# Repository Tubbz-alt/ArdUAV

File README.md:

<br />

Code repository for ground station and flight control software for experimental Arduino UAVs (fixed wing).

# [Flight Test!](https://youtu.be/rPLp50zgQIw)

See https://forum.flitetest.com/index.php?threads/arduino-scratch-build-screamin-seagull-ii.57977/ for the most recent ArdUAV plane build log.

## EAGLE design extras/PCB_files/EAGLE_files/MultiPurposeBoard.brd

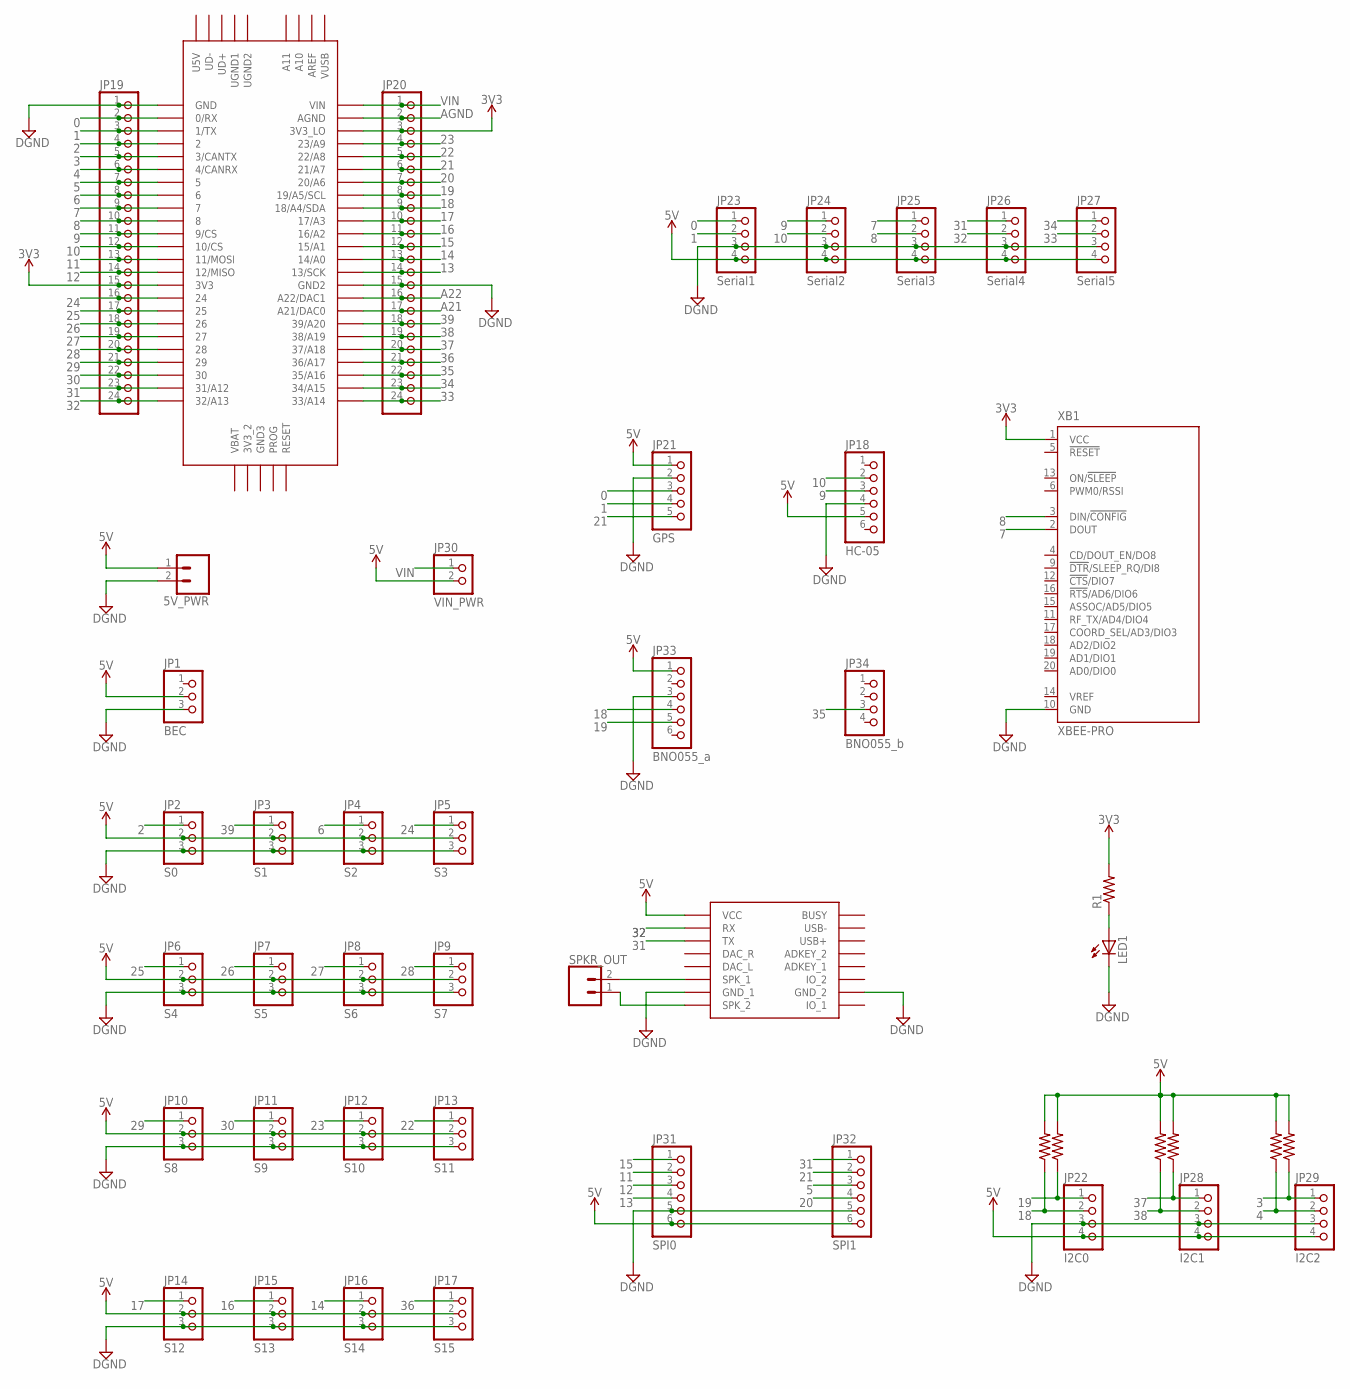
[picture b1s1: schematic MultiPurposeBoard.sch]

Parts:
5V_PWR: CONN_025MM; SCREWTERMINAL-5MM-2
JP1: BEC; 1X03
JP2: S0; 1X03
JP3: S1; 1X03
JP4: S2; 1X03
JP5: S3; 1X03
JP6: S4; 1X03
JP7: S5; 1X03
JP8: S6; 1X03
JP9: S7; 1X03
JP10: S8; 1X03
JP11: S9; 1X03
JP12: S10; 1X03
JP13: S11; 1X03
JP14: S12; 1X03
JP15: S13; 1X03
JP16: S14; 1X03
JP17: S15; 1X03
JP18: HC-05; 1X06
JP19, JP20: PINHD-1X24; 1X24
JP21: GPS; 1X05
JP22: I2C0; 1X04
JP23: Serial1; 1X04
JP24: Serial2; 1X04
JP25: Serial3; 1X04
JP26: Serial4; 1X04
JP27: Serial5; 1X04
JP28: I2C1; 1X04
JP29: I2C2; 1X04
JP30: VIN_PWR; 1X02
JP31: SPI0; 1X06
JP32: SPI1; 1X06
JP33: BNO055_a; 1X06
JP34: BNO055_b; 1X04
LED1: LED5MM
R1, R2, R3, R4, R5, R6, R7: R-US_0207/12; 0207/12
SPKR_OUT: CONN_025MM; SCREWTERMINAL-5MM-2
U$1: TEENSY_3.5/3.6
U$2: DFPLAYER
XB1: XBEE-PRO

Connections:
0: JP19.2, JP21.3, JP23.1, U$1.0/RX
1: JP19.3, JP21.4, JP23.2, U$1.1/TX
2: JP2.1, JP19.4, U$1.2
3: JP19.5, JP29.1, R5.1, U$1.3/CANTX
4: JP19.6, JP29.2, R7.1, U$1.4/CANRX
5: JP19.7, JP32.3, U$1.5
5V: 5V_PWR.1, JP1.2, JP2.2, JP3.2, JP4.2, JP5.2, JP6.2, JP7.2, JP8.2, JP9.2, JP10.2, JP11.2, JP12.2, JP13.2, JP14.2, JP15.2, JP16.2, JP17.2, JP18.5, JP21.1, JP22.4, JP23.4, JP24.4, JP25.4, JP26.4, JP27.4, JP28.4, JP29.4, JP30.2, JP31.6, JP32.6, JP33.1, R2.2, R3.2, R4.2, R5.2, R6.2, R7.2, U$2.VCC
6: JP4.1, JP19.8, U$1.6
7: JP19.9, JP25.1, U$1.7, XB1.2 (DOUT)
8: JP19.10, JP25.2, U$1.8, XB1.3 (DIN/!CONFIG)
9: JP18.3, JP19.11, JP24.1, U$1.9/CS
10: JP18.2, JP19.12, JP24.2, U$1.10/CS
11: JP19.13, JP31.2, U$1.11/MOSI
12: JP19.14, JP31.3, U$1.12/MISO
13: JP20.14, JP31.4, U$1.13/SCK
14: JP16.1, JP20.13, U$1.14/A0
15: JP20.12, JP31.1, U$1.15/A1
16: JP15.1, JP20.11, U$1.16/A2
17: JP14.1, JP20.10, U$1.17/A3
18: JP20.9, JP22.2, JP33.4, R2.1, U$1.18/A4/SDA
19: JP20.8, JP22.1, JP33.5, R3.1, U$1.19/A5/SCL
20: JP20.7, JP32.4, U$1.20/A6
21: JP20.6, JP21.5, JP32.2, U$1.21/A7
22: JP13.1, JP20.5, U$1.22/A8
23: JP12.1, JP20.4, U$1.23/A9
24: JP5.1, JP19.16, U$1.24
25: JP6.1, JP19.17, U$1.25
26: JP7.1, JP19.18, U$1.26
27: JP8.1, JP19.19, U$1.27
28: JP9.1, JP19.20, U$1.28
29: JP10.1, JP19.21, U$1.29
30: JP11.1, JP19.22, U$1.30
31: JP19.23, JP26.1, JP32.1, U$1.31/A12, U$2.TX
32: JP19.24, JP26.2, U$1.32/A13, U$2.RX
33: JP20.24, JP27.2, U$1.33/A14
34: JP20.23, JP27.1, U$1.34/A15
35: JP20.22, JP34.3, U$1.35/A16
36: JP17.1, JP20.21, U$1.36/A17
37: JP20.20, JP28.1, R6.1, U$1.37/A18
38: JP20.19, JP28.2, R4.1, U$1.38/A19
39: JP3.1, JP20.18, U$1.39/A20
A21: JP20.17, U$1.21/DAC0 (A21/DAC0)
A22: JP20.16, U$1.A22/DAC1
AGND: JP20.2, U$1.AGND
DGND: 5V_PWR.2, JP1.3, JP2.3, JP3.3, JP4.3, JP5.3, JP6.3, JP7.3, JP8.3, JP9.3, JP10.3, JP11.3, JP12.3, JP13.3, JP14.3, JP15.3, JP16.3, JP17.3, JP18.4, JP19.1, JP20.15, JP21.2, JP22.3, JP23.3, JP24.3, JP25.3, JP26.3, JP27.3, JP28.3, JP29.3, JP31.5, JP32.5, JP33.3, LED1.K (C), U$1.GND, U$1.GND2, U$2.GND_1, U$2.GND_2, XB1.10 (GND)
unnamed: LED1.A, R1.1
unnamed: SPKR_OUT.2, U$2.SPK1 (SPK_1)
unnamed: SPKR_OUT.1, U$2.SPK2 (SPK_2)
VCC_2: JP19.15, JP20.3, R1.2, U$1.3V3, U$1.3V3_LO, XB1.1 (VCC)
VIN: JP20.1, JP30.1, U$1.VIN

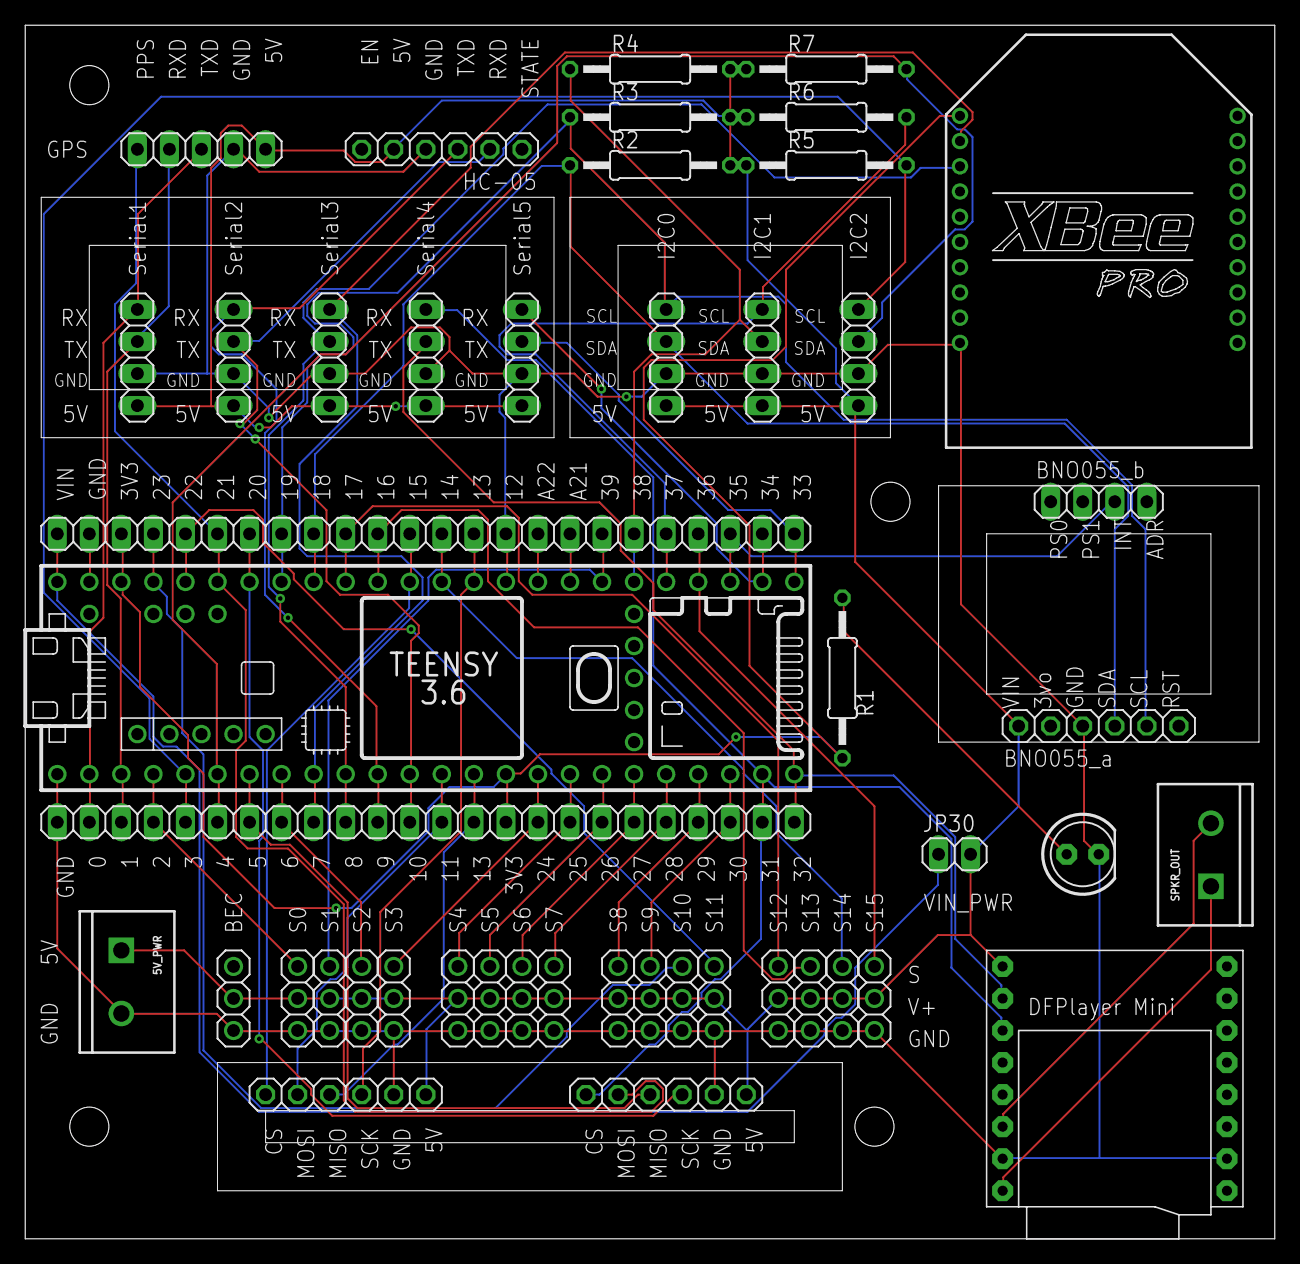
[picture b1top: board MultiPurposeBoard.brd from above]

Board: 2 copper layers, 99.0 x 96.2 mm, 47 parts (0 on the bottom side), 50 nets.

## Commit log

2019-04-17 Rename ArdUAV_Config/git_ArdUAV.bat to git_ArdUAV.bat
2019-04-20 Update and rename ArdUAV_Adafruit_PWMServoDriver.cpp to d
2019-06-22 Simplified serialEvent() contents
2019-06-22 Simplify serialEvent() contents
2019-06-22 Formatting
2019-06-22 Format
2019-06-22 Deconflict function names
2019-06-22 Deconflict function name
2019-06-22 bug fix
2019-07-06 spacing stuff/#pragma once
2019-07-31 Check Serial port compatibility at compile time
2019-07-31 Check compatible bauds for concurrent Serial port connections
2019-07-31 IDE Library Manager Compatibility Changes
2019-08-30 Added COBS encoding/decoding
2019-08-30 Parse UTC pieces
2019-08-30 Update telemetry struct
2019-08-30 Full GPS telemetry functionality added
2019-09-02 Rename extras/PCB_files/empty.txt to extras/PCB_files/Screamin_Eagle_II_files/empty.txt
2019-09-07 Added limits for extra servos
2019-09-07 Telemetry bug fixes
2019-09-08 Address Issue #9 - Increase IMU reading accuracy
    Calculate Euler angles from quaternions MCU-side instead of sensor-side
2019-09-08 Added Logo
2019-10-04 Added support for more NMEA sentences
2019-10-06 Deleted extra whitespace
2019-10-11 Default settings changes
2019-10-27 Added config file functionality
2019-10-27 Changed quotes to JSON format
2019-10-27 Added ability to save config file with custom name
2019-10-27 Added icon
2019-10-28 Bug fixes
2019-12-11 Bug fixes/changes in default settings
2019-12-11 Got rid of extra imports
2019-12-11 Changed defaults
2019-12-11 More bug fixes
2019-12-21 Replace checksum with CRC-8
2020-01-09 Specify library dependencies in library.properties (#13)
    Specifying the library dependencies in the depends field of library.properties causes the Arduino Library Manager (Arduino IDE 1.8.10 and newer) to offer to install any missing dependencies during in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
2020-01-12 Add files for exe building
2020-01-12 Simplify Dependencies (#14)
    * Delete ArdUAV_neo6mGPS.h
    * Delete ArdUAV_neo6mGPS.cpp
    * Delete CRC.h
    * Delete ArdUAV_SerialTransfer.h
    * Delete ArdUAV_SerialTransfer.cpp
    * Update library.properties
2020-01-12 Simplify serial interface (#15)
    * Update Shared_Tools.h
    * Update IFC_Tools.cpp
    * Update IFC_Serial.cpp
    * Update GS_Tools.cpp
    * Update GS_Serial.cpp
2020-01-23 Add reserved fields in the RX and TX buffers
2020-01-26 Transition to using FireTimers
2020-03-03 Rename Adafruit_Sensor.h to src/Adafruit_Sensor.h
2020-03-03 Rename ArdUAV_Adafruit_BNO055.cpp to src/ArdUAV_Adafruit_BNO055.cpp
2020-03-03 Rename ArdUAV_Adafruit_BNO055.h to src/ArdUAV_Adafruit_BNO055.h
2020-03-03 Rename ArdUAV_LIDARLite.cpp to src/ArdUAV_LIDARLite.cpp
2020-03-03 Rename ArdUAV_LIDARLite.h to src/ArdUAV_LIDARLite.h
2020-03-03 Rename GS_Serial.cpp to src/GS_Serial.cpp
2020-03-03 Rename GS_Serial.h to src/GS_Serial.h
2020-03-03 Rename vector.h to src/vector.h
2020-03-03 Rename quaternion.h to src/quaternion.h
2020-03-03 Rename matrix.h to src/matrix.h
2020-03-03 Rename imumaths.h to src/imumaths.h
2020-03-03 Rename Shared_Tools.h to src/Shared_Tools.h
2020-03-03 Rename Shared_Tools.cpp to src/Shared_Tools.cpp
2020-03-03 Rename IFC_Tools.h to src/IFC_Tools.h
2020-03-03 Rename IFC_Tools.cpp to src/IFC_Tools.cpp
2020-03-03 Rename GS_Tools.h to src/GS_Tools.h
2020-03-03 Rename IFC_Serial.h to src/IFC_Serial.h
2020-03-03 Rename GS_Tools.cpp to src/GS_Tools.cpp
2020-03-03 Rename IFC_Serial.cpp to src/IFC_Serial.cpp
2020-05-22 Notify when initialization complete
2020-06-15 Link timeout timer bug fix
2020-06-15 Dev (#16)
    * Delete IFC_Serial.cpp
    * Add files via upload
    * Link timeout bug fix
2020-07-07 Update due to SerialTransfer.h updates
2020-07-28 Overhaul
2020-08-04 Update ArdUAV_Config script to reflect base lib changes

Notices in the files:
parts and their libraries:
SparkFun-Retired: Licensing: Creative Commons ShareAlike 4.0 International - https://creativecommons.org/licenses/by-sa/4.0
